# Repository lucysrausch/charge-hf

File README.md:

# GaN Class-D Wireless Power Amplifier

I designed this board because I wanted a signal generator that was more capable than just generating a static waveform.
For familiarizing myself with wireless power transfer and getting a feeling for antenna and magnetic design, I wanted a source-meausure-unit (SMU) for RF,
something that could generate and also measure RF output. I also wanted all settings and measurements to be easily controllable and readable such that I could easily script testbenches in python for plotting parameter sweeps, or prototype control loops critical for real-world WPT like resonance tracking or constant output power control.

I finished this project in winter 2020, and it became an invaluable tool throughout 2021 for designing a custom wireless charging solution.

*Assembled development board showing real-time status on OLED display: frequency, RF power, and VSWR measurements.*
*Demonstration setup: PCB spiral coil antennas (transmit and receive) wirelessly powering an LED strip at 6.78 MHz.

## Features

- **6.78 MHz ISM Band Operation** - Optimized for the AirFuel/Qi extended power profile frequency band
- **Software-Defined RF Generation** - Real-time frequency and deadtime adjustment via software
- **STM32G4 HRTIM** - Built around the STM32G474 with 184 ps RF PWM resolution (5.4 GHz effective clock)
- **Integrated SEPIC Converter** - Programmable amplifier supply voltage (0–20V) with input current limiting
- **SCPI over USB CDC** - Standard instrument control protocol for automated test benches
- **OLED Status Display** - Real-time frequency, power, and VSWR monitoring
- **Analog Knob Inputs** - Two potentiometers which can be read via SCPI to control any parameter. (or you can use these ADC inputs to measure ie. voltage and current in the WPT receiver and plot them along input power for efficiency sweeps

## Applications

- Wireless power transfer research and development
- Antenna impedance matching and tuning, efficiency testing
- Inductive heating experiments, plasma generation
- Generic educational RF / power electronics platform

## Hardware Specifications

| Parameter | Value |
|-----------|-------|
| Operating Frequency | 10 kHz – 10 MHz |
| HRTIM Resolution | 184 ps (144 MHz × 32 multiplier) |
| Deadtime Range | 0–511 counts (×8 prescaler, ~1.1 ns steps) |
| Amplifier Supply | 0–20V (SEPIC regulated) |
| Input Current Limit | Programmable, default 3A |
| Input Voltage | 5V USB-C |
| Control Interface | USB CDC (Virtual COM Port) |
| MCU | STM32G474 (170 MHz Cortex-M4F) |

## PCB Design

### 3D Rendering

*3D render of the assembled board with all components*

### Board Layout

*Full board layout showing component placement: USB-C input (left), OLED display, SEPIC converter (top right), STM32G4 MCU, GaN half-bridge (center right), and output matching network (bottom right)*

### Critical Design: Ground Plane and Return Path

*PCB layout highlighting the ground plane structure around the GaN switching stage*

High-frequency switching at 6.78 MHz with fast edge rates demands careful attention to parasitic inductance in the power loop. Key design decisions implemented in this layout:

**Minimizing Loop Inductance:**
- **Tight Component Placement** - The GaN FETs, gate drivers, and decoupling capacitors are placed as close as possible to minimize the physical area of the switching current loop
- **Direct Via Stitching** - Multiple vias connect the top-side ground pads directly to the internal ground plane, reducing the inductance of the return path
- **Solid Ground Reference** - An unbroken ground plane beneath the switching node provides a low-inductance return path for high-frequency currents with a single net tie to DGND
- **Thermal Relief Considerations** - Ground connections to the FET source pads use sufficient via count to handle both thermal dissipation and the high-frequency return currents

## Schematic

📄 **[Download Full Schematic (PDF)](hardware/schematic_V1.2/charge-hf.pdf)**

The schematic is organized into functional blocks:

```
┌─────────────────┐   ┌─────────────────┐   ┌─────────────────┐   ┌─────────────────┐
│   USB-C Input   │──▶│   SEPIC DCDC    │──▶│  GaN Half-Bridge│──▶│   RF Output     │
│   + ESD Prot.   │   │   5V → 0-20V    │   │   LMG5200       │   │   I & U Sense   │
└────────┬────────┘   └────────┬────────┘   └────────┬────────┘   └─────────────────┘
         │                     │                     │
         │            ┌────────┴────────┐            │
         └───────────▶│   STM32G474     │-───────────┘
                      │   HRTIM + ADC   │
                      │   USB CDC SCPI  │
                      └─────────────────┘
```

## Circuit Design Notes

### Power Stage: LMG5200 GaN Half-Bridge

The heart of the RF amplifier is the **Texas Instruments LMG5200**, a fully integrated 80V/10A GaN half-bridge power stage. This device integrates both high-side and low-side GaN FETs along with their gate drivers in a single 6×8mm QFN package.

**Why use an integrated module?**

- **Minimized Parasitics** - The gate driver and GaN FETs are co-packaged with optimized bond wire lengths, achieving lower gate loop inductance than any discrete solution. This is critical at 6.78 MHz where even 1nH of stray inductance causes significant ringing.
- **Simplified Layout** - A single component eliminates the need to route high-speed gate drive signals across the PCB, reducing EMI and layout complexity.

### SEPIC DC-DC Converter

The amplifier supply (VPP) is generated by a SEPIC topology, chosen for its ability to both step-up and step-down. This allows operation from 5V USB while generating 0–20V for the GaN stage.

**Key components:**

- **Si4058 (Q1)** - Low Rds(on) N-channel MOSFET handles the primary switching
- **MIC4416 (U3)** - Low-side gate driver with enable control, driven directly from STM32 HRTIM Timer D

**Feedback and control:**

- **Voltage Sensing** - A resistive divider (100k/5.1k) scales VPP down to ADC range
- **Current Sensing** - A 10mΩ shunt (R13) with a Si8540 current sense amplifier measures input current for overcurrent protection and constant power control
- **Digital Control Loop** - The STM32 implements a PI controller in the HRTIM repetition interrupt, adjusting duty cycle based on voltage error with current limiting

### USB Power Input

The design operates from USB-C with proper PD support:

- **USBLC6-4 (U2)** - ESD protection on D+/D- and CC lines
- **CC1/CC2 Resistors (R3, R4)** - 5.1kΩ pull-downs advertise the device as a UFP (sink) for default 5V/3A
- **UCPD Peripheral** - The STM32G4's built-in USB-PD controller connects to CC1/CC2 for potential USB-PD negotiation (firmware support for higher voltages possible)

### RF Output Network

The Class-D output is filtered and can be impedance-matched to an antenna:

- **LC Resonant Tank (L1, L2, C29)** - Two 390nH inductors and a 1µF capacitor form a series-resonant network tuned near 6.78 MHz. The tank filters the square wave output and provides the sinusoidal current needed for efficient WPT.
- **CST7030-020LB (T2)** - A 1:20 turns ratio current transformer plus shunt resistor are used for sensing AC output current

### STM32G474 Configuration

The STM32G474CB provides the digital control:

- **HRTIM Timer C** - Generates complementary PWM for the GaN half-bridge with programmable deadtime
- **HRTIM Timer D** - Drives the SEPIC converter with separate frequency/duty control
- **ADC2** - Continuous DMA-driven sampling of voltages, currents, and potentiometer inputs
- **DAC1/DAC3** - Provide reference voltages for the analog comparators (overcurrent protection)
- **I2C1** - Drives the OLED status display
- **USB** - CDC virtual COM port for SCPI communication

## SCPI Command Reference

The amplifier implements SCPI (Standard Commands for Programmable Instruments) over USB CDC. Connect using any serial terminal or VISA library at the default USB CDC settings.

### Identification Commands

| Command | Description | Example Response |
|---------|-------------|------------------|
| `*IDN?` | Query device identification | `Manufacturer,Model,Serial,Version` |
| `*RST` | Reset device to default state | - |
| `*TST?` | Self-test query | `0` (pass) or `1` (fail) |
| `*CLS` | Clear status registers | - |
| `*OPC?` | Operation complete query | `1` |

### Measurement Commands

| Command | Description | Returns |
|---------|-------------|---------|
| `MEASure:VOLTage:DC:INput?` | Read USB input voltage | Voltage in V (float) |
| `MEASure:VOLTage:DC:OUTput?` | Read amplifier supply voltage | Voltage in V (float) |
| `MEASure:CURRent:DC:INput?` | Read input current | Current in A (float) |
| `MEASure:VOLTage:DC:CONTrol? <n>` | Read potentiometer voltage | Voltage in V (float) |

**Example:**
```
> MEAS:VOLT:DC:IN?
< 5.032

> MEAS:VOLT:DC:OUT?
< 12.45

> MEAS:CURR:DC:IN?
< 0.856

> MEAS:VOLT:DC:CONT? 1
< 1.65
```

### Configuration Commands

| Command | Parameters | Description |
|---------|------------|-------------|
| `CONFigure:VOLTage:DC:OUTput <V>` | Voltage (0–30V) | Set amplifier supply voltage |
| `CONFigure:CURRent:DC:INput <A>` | Current (0–3A) | Set input current limit |
| `CONFigure:FREQuency <Hz>` | Frequency (10000–15000000) | Set RF output frequency |
| `CONFigure:DEADtime <rising>,<falling>` | 0–511 each | Set half-bridge deadtime |

**Example:**
```
> CONF:VOLT:DC:OUT 15
< OK

> CONF:FREQ 6780000
< OK

> CONF:DEAD 20,20
< OK
```

### System Commands

| Command | Description |
|---------|-------------|
| `SYSTem:ERRor?` | Query and clear oldest error |
| `SYSTem:ERRor:COUNt?` | Query number of errors in queue |
| `SYSTem:VERSion?` | Query SCPI version |
| `STATus:QUEStionable?` | Query questionable status register |

## Python Examples

Example scripts are provided in the [`software/`](software/) directory demonstrating SCPI communication via PyVISA.

Thanks to SCPI integration for both setting parameters and reading output power, it is very easy to build custom testbenches to characterize ie. efficiency over frequency and plot the results using matplotlib or similar.

### Basic Control - [`control.py`](software/control.py)

This script provides interactive control using the two onboard potentiometers. It continuously reads the knob positions via `MEAS:VOLT:DC:CONTrol?`, maps them to frequency (1–8 MHz) and output voltage (0–30V), and updates the amplifier settings in real-time. The display shows actual measured values including calculated input power.

**Usage:**
```bash
python software/control.py
```

### Custom Scripts

For custom automation, connect using PyVISA with the `@py` backend:

```python
import pyvisa as visa
rm = visa.ResourceManager('@py')
amp = rm.open_resource("ASRL/dev/ttyACM0::INSTR")
print(amp.query("*IDN?"))
```

On Windows, the resource string will be `ASRL<n>::INSTR` where `<n>` is the COM port number assigned to the USB CDC device.

## Building the Firmware

### Prerequisites

- ARM GCC Toolchain
- STM32CubeMX (for regenerating HAL code if needed)
- OpenOCD or ST-Utils for flashing

### Compilation

```bash
cd firmware
make
```

### Flashing

```bash
# Using OpenOCD
openocd -f interface/stlink.cfg -f target/stm32g4x.cfg -c "program build/main.elf verify reset exit"

# Or using ST-Link utility
st-flash write build/main.bin 0x8000000
```

### Known bugs

The board features a push button connected to the boot select pin of the STM32. In theory, this would allow the STM32 to enter DFU mode and allow to flash the board without the need for a programmer. Unfortunatly, despite a strong pull-down resistor, the GPIO connected to the gate driver for the SEPIC DC-DC seems to go high when entering DFU. This turns on Q1, but without PWM, it just shorts the USB input and triggers an overcurrent event on the USB port the device is plugged into.

The workaround is to simply not assemble this button, and always flash the board via SWD.

## License

- Hardware design files: MIT license 
- Firmware: MIT license 
- Software: MIT license
- 3rd party Firmware: BSD 3-Clause (STM32 HAL), BSD 2-Clause (SCPI library)

## Author

Lucy Fauth - Rev 1.2 (February 2021)

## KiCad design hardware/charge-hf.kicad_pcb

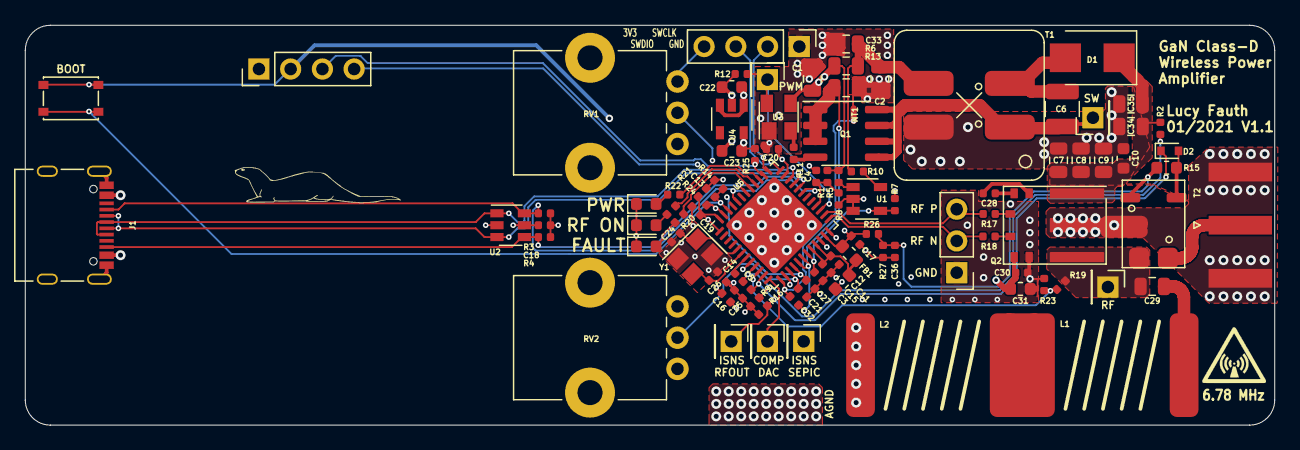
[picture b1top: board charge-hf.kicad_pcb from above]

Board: 4 copper layers, 100.0 x 32.0 mm, 96 parts (0 on the bottom side), 55 nets.

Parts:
C1, C2, C33: 10u 35V; C_0805_2012Metric
C3, C4, C5, C13, C14, C15, C21, C25, C27: 1n; C_0402_1005Metric
C6: 10u 35V; C_1210_3225Metric
C7, C8, C9, C34, C35: 1u 100V; C_0805_2012Metric
C10: 10n; C_0603_1608Metric
C11, C16, C17, C18, C19, C20, C28, C30, C36: 100n; C_0402_1005Metric
C12, C22, C23: 10u; C_0603_1608Metric
C24, C26, C32: 18p; C_0402_1005Metric
C29: 1u 50V; C_0805_2012Metric
C31: 1u; C_0603_1608Metric
D1: MBRS1100T 3G; D_SMB
D2: SDM03U40; D_SOD-523
FB1: 601; L_0603_1608Metric
J1: USB_C_Receptacle_USB2.0; USB_C_Receptacle_Palconn_UTC16-G
J2, J3, J4, J7, J8, J9: TP; PinHeader_1x01_P2.54mm_Vertical
J5: SMA; SMA_Amphenol_132289_EdgeMount
J6: HF; PinHeader_1x03_P2.54mm_Vertical
J10: DEBUG; PinHeader_1x04_P2.54mm_Vertical
J11: OLED; PinHeader_1x04_P2.54mm_Vertical
L1, L2: 390nH; 2929SQ
LED1, LED2, LED3: FAULT; LED_0603_1608Metric
NT1: GND; NetTie-2_SMD_Pad0.5mm
Q1: Si4058; SOIC-8_3.9x4.9mm_P1.27mm
Q2: LMG5200; Texas_MOF0009A
R1, R8, R9, R12, R24, R25, R26: 5k1; R_0402_1005Metric
R2, R16, R19: 100k; R_0402_1005Metric
R3, R4: DNP; R_0402_1005Metric
R5, R10: 33; R_0402_1005Metric
R6, R13: 10m; R_0805_2012Metric
R7, R14, R20, R21, R22, R23, R27: 2k; R_0402_1005Metric
R11: 2.2R; R_0402_1005Metric
R15: 49.9R; R_0603_1608Metric
R17, R18: 22R; R_0402_1005Metric
RV1, RV2: 10k; Potentiometer_Bourns_PTV09A-1_Single_Vertical
SW1: DFU; SW_SPST_PTS810
T1: MSD1260
T2: CST7030-020LB 1:20; CST7030
U1: Si8540; SOT-23-5
U2: USBLC6-4; SOT-23-6
U3: MIC4416; SOT-143
U4: MIC5504-3.3YM5; SOT-23-5
U5: STM32G474CBUx; QFN-48-1EP_7x7mm_P0.5mm_EP5.6x5.6mm
Y1: 8MHz; Crystal_SMD_3225-4Pin_3.2x2.5mm

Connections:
+3V3: C16.2, C17.2, C18.2, C19.2, C20.2, C23.1, FB1.2, J10.4, J11.2, R24.1, R25.1, R26.1, RV1.1, RV2.1, SW1.1, U2.5, U4.5, U5.1, U5.23, U5.35, U5.48
+5V: C1.1, C22.1, C30.2, C31.2, J1.A4, J1.A9, J1.B4, J1.B9, Q2.6, R1.1, R5.2, R6.1, U3.3, U4.1, U4.3
BOOT: C13.2, R14.1, SW1.2, U5.46
DAC1: J7.1, U5.12
GND: C1.2, C2.2, C3.2, C4.2, C5.2, C11.2, C12.2, C13.1, C14.1, C15.1, C16.1, C17.1, C18.1, C19.1, C20.1, C21.1, C22.2, C23.2, C24.1, C25.1, C26.1, C27.1, C30.1, C31.1, C33.2, C36.1, J1.A1, J1.A12, J1.B1, J1.B12, J1.S1, J6.1, J10.1, J11.1, LED1.1, LED2.1, LED3.1, NT1.1, Q2.7, R3.2, R4.2, R7.2, R8.2, R9.2, R12.2, R13.2, R14.2, R16.2, R23.2, R27.2, RV1.3, RV2.3, U1.2, U1.3, U2.2, U3.1, U4.2, U5.49, Y1.2, Y1.4
GNDS: C7.2, C8.2, C9.2, C10.2, C34.2, C35.2, J5.2, L2.2, Q2.9, T1.4
I2C_SCL: J11.3, R25.2, U5.38
I2C_SDA: J11.4, R24.2, U5.47
LED1: R20.1, U5.41
LED2: R21.1, U5.40
LED3: R22.1, U5.39
unnamed: C6.1, D1.2, T1.2
unnamed: C6.2, J2.1, Q1.5, Q1.6, Q1.7, Q1.8, T1.1
unnamed: C11.1, C12.1, C15.2, FB1.1, U5.20, U5.21
unnamed: C24.2, U5.5, Y1.1
unnamed: C26.2, U5.6, Y1.3
unnamed: C28.1, Q2.2
unnamed: C28.2, Q2.3
unnamed: C29.1, L1.1
unnamed: C29.2, J4.1, Q2.8, R19.1, T2.3
unnamed: C36.2, R15.2, R26.2, R27.1, T2.2
unnamed: D2.2, R15.1, T2.1
unnamed: J5.1, T2.4
unnamed: L1.2, L2.1
unnamed: LED1.2, R20.2
unnamed: LED2.2, R21.2
unnamed: LED3.2, R22.2
unnamed: Q1.4, R11.1
unnamed: Q2.4, R17.1
unnamed: Q2.5, R18.1
unnamed: R5.1, U1.1
unnamed: R10.1, U1.5
unnamed: R11.2, U3.2
POTI1: C21.2, RV2.2, U5.15
POTI2: C27.2, RV1.2, U5.16
RESET: C14.2, U5.7
RF_ISNS: C25.2, D2.1, J3.1, R16.1, U5.8, U5.11
RF_N: J6.2, R18.2, U5.25
RF_P: J6.3, R17.2, U5.26
RF_VSNS: R19.2, R23.1, U5.10
SEPIC_ISNS_N: C32.2, NT1.2, U5.13
SEPIC_ISNS_OUT: J9.1, U5.14
SEPIC_ISNS_P: C32.1, Q1.1, Q1.2, Q1.3, R13.1, U5.17, U5.18
SEPIC_PWM: J8.1, R12.1, U3.4, U5.27
SEPIC_VSNS: C5.1, R2.2, R9.1, U5.9
SWCLK: J10.2, U5.37
SWDIO: J10.3, U5.36
UCPD_CC1: J1.A5, R3.1, U2.6, U5.31, U5.44
UCPD_CC2: J1.B5, R4.1, U2.4, U5.32, U5.42
USB_DN: J1.A7, J1.B7, U2.3, U5.33
USB_DP: J1.A6, J1.B6, U2.1, U5.34
USB_ISNS: C3.1, R7.1, U1.4, U5.19
USB_VSNS: C4.1, R1.2, R8.1, U5.28
VBUS: C7.1, C8.1, C9.1, C10.1, C34.1, C35.1, D1.1, Q2.1, R2.1
VPP: C2.1, C33.1, R6.2, R10.2, T1.3

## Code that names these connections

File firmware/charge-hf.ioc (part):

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Mcu.Name=STM32G474C(B-C-E)Ux
Mcu.Package=UFQFPN48
Mcu.UserName=STM32G474CBUx
PA0.Mode=INP
PA0.Signal=COMP3_INP
PA1.Mode=IN2-Single-Ended
PA1.Signal=ADC2_IN2
PA10.Mode=EnableDeadBattery
PA10.Signal=UCPD1_DBCC2
PA11.Mode=Device
PA11.Signal=USB_DM
PA12.Mode=Device
PA12.Signal=USB_DP
PA13.Mode=Serial_Wire
PA13.Signal=SYS_JTMS-SWDIO
PA14.Mode=Serial_Wire
PA14.Signal=SYS_JTCK-SWCLK
PA15.Mode=I2C
PA15.Signal=I2C1_SCL
PA2.Mode=IN3-Single-Ended
PA2.Signal=ADC1_IN3
PA3.Mode=PGA_Internally_Connected
PA3.Signal=OPAMP1_VINP
PA4.Signal=COMP_DAC11_group
PA7.Mode=IN4-Single-Ended
PA7.Signal=ADC2_IN4
PA9.Mode=EnableDeadBattery
PA9.Signal=UCPD1_DBCC1
PB1.Mode=INP
PB1.Signal=COMP1_INP
PB12.Mode=Output_TC1TC2
PB12.Signal=HRTIM1_CHC1
PB13.Mode=Output_TC1TC2
PB13.Signal=HRTIM1_CHC2
PB14.Mode=Output_TD1
PB14.Signal=HRTIM1_CHD1
PB15.Mode=IN15-Single-Ended
PB15.Signal=ADC2_IN15
PB2.Mode=IN12-Single-Ended
PB2.Signal=ADC2_IN12
PB3.GPIOParameters=GPIO_Label
PB3.GPIO_Label=LED1
PB3.Signal=GPIO_Output
PB4.Mode=Sink_AllSignals
PB4.Signal=UCPD1_CC2
PB5.Signal=GPIO_Output
PB6.Mode=Sink_AllSignals
PB6.Signal=UCPD1_CC1
PB7.Signal=GPIO_Output
PB8-BOOT0.GPIOParameters=GPIO_Label
PB8-BOOT0.GPIO_Label=BOOT
PB8-BOOT0.Signal=GPIO_Input
PB9.Mode=I2C
PB9.Signal=I2C1_SDA
PC10.GPIOParameters=GPIO_Label
PC10.GPIO_Label=LED3
PC10.Signal=GPIO_Output
PC11.GPIOParameters=GPIO_Label
PC11.GPIO_Label=LED2
PC11.Signal=GPIO_Output
PC4.Mode=IN5-Single-Ended
PC4.Signal=ADC2_IN5
PF0-OSC_IN.Mode=HSE-External-Oscillator
PF0-OSC_IN.Signal=RCC_OSC_IN
PF1-OSC_OUT.Mode=HSE-External-Oscillator
PF1-OSC_OUT.Signal=RCC_OSC_OUT
RCC.HSE_VALUE=8000000
RCC.SYSCLKFreq_VALUE=144000000
RCC.SYSCLKSource=RCC_SYSCLKSOURCE_PLLCLK
board=custom

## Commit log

2021-02-12 Add SCPI lib and USB CDC support
2021-02-12 SCPI working
2021-02-13 Make SCPI assynchronious so TX would work
2021-02-13 Add Readme
2021-02-13 Add python control example
2021-02-13 Add SCPI speed test
2021-02-13 Add ADC2 continious regular conversion for knobs and SCPI config functions for sepic parameters
2021-02-15 Added configure frequency and deadtime command, debugged HRTIM
2021-02-20 add kicad design files
2021-02-20 moved gitignore
2021-02-20 add 3d step file
2025-12-02 ADD: pictures and refactored schematic
2025-12-02 Add LICENSE
2025-12-02 Update license unformation
